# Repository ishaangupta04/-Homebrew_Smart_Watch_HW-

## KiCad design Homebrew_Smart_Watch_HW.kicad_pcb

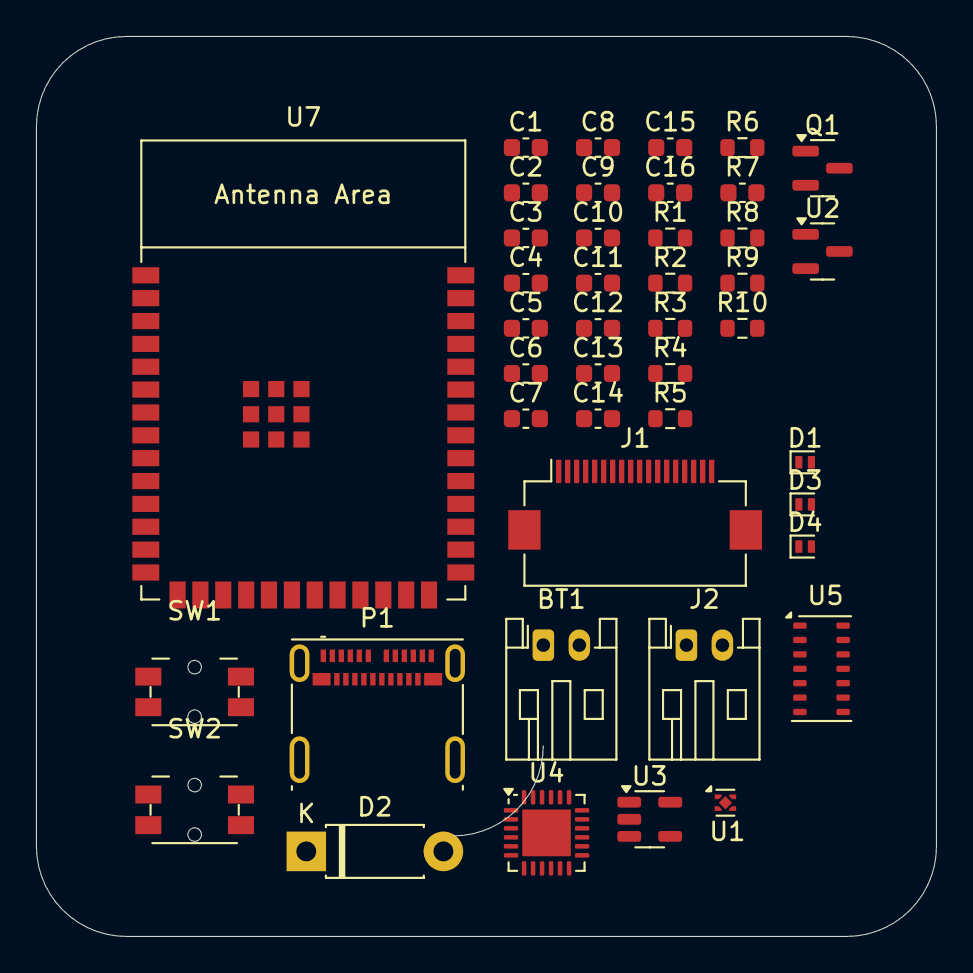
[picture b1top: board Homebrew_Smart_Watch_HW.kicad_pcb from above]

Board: 2 copper layers, 50.0 x 50.0 mm, 43 parts (0 on the bottom side), 27 nets, no tracks yet.

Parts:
BT1: Battery_Cell; JST_PH_S2B-PH-K_1x02_P2.00mm_Horizontal
C1, C2, C4, C6, C13, C15: 1uF; C_0603_1608Metric
C3, C5: 0.1uF; C_0603_1608Metric
C7, C10: 4.7uF; C_0603_1608Metric
C8: 10 nF; C_0603_1608Metric
C9, C12: 0.1 uF; C_0603_1608Metric
C11: 2.2 nF; C_0603_1608Metric
C14: .1uF; C_0603_1608Metric
C16: C_Small; C_0603_1608Metric
D1, D3: D_SOD-882
D2: D_Schottky; D_DO-41_SOD81_P7.62mm_Horizontal
D4: SD05_SOD323; D_SOD-882
J1: Conn_01x18_Pin; Hirose_FH12-18S-0.5SH_1x18-1MP_P0.50mm_Horizontal
J2: Conn_01x02_Pin; JST_PH_S2B-PH-K_1x02_P2.00mm_Horizontal
P1: USB_C_Plug_USB2.0; USB_C_Receptacle_Molex_105450-0101
Q1: PMOS; SOT-23
R1, R2: 5.1K; R_0603_1608Metric
R3, R6, R8: 10k; R_0603_1608Metric
R4, R5: 4.7K; R_0603_1608Metric
R7: 10k; C_0603_1608Metric
R9, R10: 22; R_0603_1608Metric
SW1: TS24CA; Panasonic_EVQPUM_EVQPUD
SW2: SW_SPST; Panasonic_EVQPUM_EVQPUD
U1: OnSemi_XDFN4-1EP_1.0x1.0mm_EP0.52x0.52mm
U2: SOT-23
U3: SOT-23-5
U4: QFN-24-1EP_4x4mm_P0.5mm_EP2.7x2.6mm
U5: MAX30102; Maxim_OLGA-14_3.3x5.6mm_P0.8mm
U7: ESP32-S2-SOLO

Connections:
+1.8V: C5.1, C6.1, U2.2 (VOUT), U5.11 (VDD)
+3.3V: C1.1, C3.1, C4.2, C8.1, C12.2, C13.2, C14.2, J1.1 (VIN), R4.2, R5.1, R7.1, R8.1, U1.1 (OUT), U2.3 (VIN), U4.8 (VLOGIC), U4.13 (VDO), U5.9 (VLED+), U5.10 (VLED+), U7.2 (3V3)
/BKL: J1.2 (BLK), U7.25 (SPIIO5/GPIO34/FSPICS0)
/Button: C15.1, SW1.2 (B), U7.27 (GPIO0)
/D+: R10.2, U7.14 (GPIO20/U1CTS/ADC2_CH9/CLK_OUT1/USB_D+)
/D-: R9.2, U7.13 (GPIO19/U1RTS/ADC2_CH8/CLK_OUT2/USB_D-)
/INT: U4.12 (INT), U7.15 (GPIO3/TOUCH3/ADC1_CH2)
/MOSI: J1.5 (MOSI), U7.23 (GPIO21)
/SCK: J1.4 (SCK), U7.24 (SPIIO4/GPIO33/FSPIHD)
/SCL: R5.2, U4.23 (SCL), U5.2 (SCL), U7.18 (GPIO10/TOUCH10/ADC1_CH9/FSPICS0/FSPIIO4)
/SDA: R4.1, U4.24 (SDA), U5.3 (SDA), U7.17 (GPIO9/TOUCH9/ADC1_CH8/FSPIHD)
/SDCS: J1.10 (SDCS), U7.19 (GPIO11/TOUCH11/ADC2_CH0/FSPID/FSPIIO5)
/TFTCS: J1.9 (TFTSPI), U7.20 (GPIO12/TOUCH12/ADC2_CH1/FSPICLK/FSPIIO6)
/TFTDC: J1.7 (TFTDC), U7.22 (GPIO14/TOUCH14/ADC2_CH3/FSPIWP/FSPIDQS)
/TFTRST: J1.8 (TFTRST), U7.21 (GPIO13/TOUCH13/ADC2_CH2/FSPIQ/FSPIIO7)
GND: BT1.2 (-), C1.2, C2.2, C3.2, C4.1, C5.2, C6.2, C7.2, C8.2, C9.2, C10.1, C11.1, C12.1, C13.1, C14.1, C15.2, C16.1, D1.2 (A2), D3.2 (A2), D4.2 (A2), J1.3 (GND), J2.2, P1.A1 (GND), P1.A12 (GND), P1.B1 (GND), P1.B12 (GND), P1.S1 (SHIELD), Q1.3 (S), R1.1, R2.2, R3.2, R6.2, SW1.1 (A), SW2.1 (A), U1.2 (GND), U1.5 (EP), U2.1 (VSS), U3.2 (VSS), U4.1 (CLKIN), U4.11 (FSYNC), U4.18 (GND), U5.4 (PGND), U5.12 (GND), U7.1 (GND), U7.40 (GND), U7.41 (GND)
unnamed: BT1.1 (+), C7.1, U3.3 (VBAT)
unnamed: D1.1 (A1), D2.2 (A), D3.1 (A1), D4.1 (A1), P1.A4 (VBUS), P1.A6 (D+), P1.A7 (D-), P1.A9 (VBUS), P1.B4 (VBUS), P1.B9 (VBUS), R9.1, R10.1
unnamed: P1.A5 (CC), R1.2
unnamed: P1.B5 (VCONN), R2.1
unnamed: C16.2, R8.2, SW2.2 (B), U7.3 (EN)
unnamed: R3.1, U3.5 (PROG)
unnamed: C11.2, U4.20 (CPOUT)
unnamed: C9.1, U4.10 (REGOUT)
unnamed: R7.2, U5.13 (~INT)
USB_VCC: C10.2, D2.1 (K), Q1.2 (G), R6.1, U3.4 (VDD)
VBAT: C2.1, J2.1, Q1.1 (D), U1.3 (EN), U1.4 (IN)

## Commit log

2024-10-23 Added Schottky footprint
2024-10-23 test
